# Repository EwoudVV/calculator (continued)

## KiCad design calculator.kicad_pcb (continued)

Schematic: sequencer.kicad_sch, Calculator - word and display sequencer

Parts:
C301, C302, C303, C304, C305, C306, C307, C308, C309, C310, C311, C312, C313, C314, C315, C316, C317, C318, C319, C320: 100n; C_0603_1608Metric
U301, U302: SN74HC163DR; SOIC-16_3.9x9.9mm_P1.27mm
U303: CD74HC173M96; SOIC-16_3.9x9.9mm_P1.27mm
U304: CD74HC157M96; SOIC-16_3.9x9.9mm_P1.27mm
U305: CD74HC139M96; SOIC-16_3.9x9.9mm_P1.27mm
U306, U309, U317: SN74HC04PWR; TSSOP-14_4.4x5mm_P0.65mm
U307, U311, U312, U313, U315, U316, U319: SN74HC08PWR; TSSOP-14_4.4x5mm_P0.65mm
U308, U314, U318: SN74HC32PWR; TSSOP-14_4.4x5mm_P0.65mm
U310: CD74HC27M96; SOIC-14_3.9x8.7mm_P1.27mm
U320: SN74HC74DR; SOIC-14_3.9x8.7mm_P1.27mm

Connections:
+5V: C301.1, C302.1, C303.1, C304.1, C305.1, C306.1, C307.1, C308.1, C309.1, C310.1, C311.1, C312.1, C313.1, C314.1, C315.1, C316.1, C317.1, C318.1, C319.1, C320.1, U301.9 (~PE), U301.10 (CET), U301.16 (VCC), U302.9 (~PE), U302.10 (CET), U302.16 (VCC), U303.16 (VCC), U304.16 (VCC), U305.16 (VCC), U306.14 (VCC), U307.14 (VCC), U308.14 (VCC), U309.14 (VCC), U310.14 (VCC), U311.5, U311.14 (VCC), U312.14 (VCC), U313.14 (VCC), U314.14 (VCC), U315.14 (VCC), U316.14 (VCC), U317.14 (VCC), U318.14 (VCC), U319.14 (VCC), U320.1 (~R), U320.10 (~S), U320.14 (VCC); also elsewhere on the board
/BANK_RESET_N: U320.6 (~Q); also elsewhere on the board
/Sequencer/ACTION_ALLOWED: U307.3, U307.5, U307.10, U315.10, U316.5, U319.2
/Sequencer/CANCEL_N: U306.12, U307.2
/Sequencer/DIGIT_ENABLE: U302.7 (CEP), U313.3
/Sequencer/DIGIT_LAST: U309.3, U311.3, U312.13, U313.5
/Sequencer/DIGIT_LOW_ONES: U307.11, U311.1
/Sequencer/DIGIT_NOT_LAST: U309.4, U313.2
/Sequencer/DIGIT_STEP: U308.11, U313.1
/Sequencer/DISPLAY_ACTIVE: U307.8, U312.1, U312.4, U314.4
/Sequencer/DISPLAY_DONE: U308.10, U312.11
/Sequencer/DISPLAY_ROTATE_A: U314.10, U315.6
/Sequencer/DISPLAY_ROTATE_B: U314.13, U316.3
/Sequencer/DISPLAY_ROTATE_N: U309.6, U313.13
/Sequencer/DISPLAY_ROTATE_W: U316.11, U318.2
/Sequencer/P0_N: U305.4 (O0), U306.1
/Sequencer/P1_N: U305.5 (O1), U306.3
/Sequencer/P2_N: U305.6 (O2), U306.5
/Sequencer/P3_N: U305.7 (O3), U306.9
/Sequencer/PHASE_0: U301.14 (Q0), U305.2 (A0)
/Sequencer/PHASE_1: U301.13 (Q1), U305.3 (A1)
/Sequencer/PHASE_ENABLE: U301.7 (CEP), U314.6
/Sequencer/PHASE_RESET_N: U301.1 (~MR), U313.11
/Sequencer/PH_CLOSE: U306.6, U312.10
/Sequencer/PH_PREP: U306.2, U311.10, U312.2, U314.1
/Sequencer/PH_ROTATE: U306.8, U312.5
/Sequencer/PH_RUN: U306.4, U311.13, U313.4
/Sequencer/POWER_RESET: U303.15 (Mr), U306.10, U308.5
/Sequencer/SEQUENCER_RESET_N: U302.1 (~MR), U309.2, U313.12
/Sequencer/SEQ_ABORT_OR_ADVANCE: U308.3, U308.4
/Sequencer/SEQ_RESET: U308.6, U309.1
/Sequencer/SOURCE_A: U309.10, U315.5
/Sequencer/SOURCE_A_N: U305.12 (O0), U309.11
/Sequencer/SOURCE_B: U309.12, U316.2
/Sequencer/SOURCE_B_N: U305.11 (O1), U309.13
/Sequencer/SOURCE_LOAD: U309.9, U315.3
/Sequencer/SOURCE_LOAD_N: U303.9 (E1), U309.8
/Sequencer/SOURCE_W: U316.13, U317.2
/Sequencer/SOURCE_W_N: U305.10 (O2), U317.1
/Sequencer/WORD_ACTIVE: U307.6, U311.9, U311.12, U312.9, U313.9
/Sequencer/WORD_DONE: U308.9, U312.8
/Sequencer/WORD_LAST_RUN: U313.6, U314.2
/Sequencer/WORD_PHASE_ENABLE: U313.8, U314.5
/Sequencer/WORD_PHASE_STEP: U313.10, U314.3
ALU_STEP: U308.12, U311.11, U314.9, U314.12, U318.1; also elsewhere on the board
A_ROTATE_RIGHT: U314.8; also elsewhere on the board
A_SHIFT_LEFT: U315.8; also elsewhere on the board
A_WRITE_ALU: U315.11; also elsewhere on the board
BANK_CLK: U301.2 (CP), U302.2 (CP), U303.7 (Cp), U320.3 (C); also elsewhere on the board
B_ROTATE_RIGHT: U314.11; also elsewhere on the board
B_SHIFT_LEFT: U316.6; also elsewhere on the board
B_WRITE_ALU: U316.8; also elsewhere on the board
CANCEL: U306.13, U308.2; also elsewhere on the board
DIGIT_FIRST: U310.12, U315.2; also elsewhere on the board
DIGIT_INDEX_0: U302.14 (Q0), U307.12, U310.1; also elsewhere on the board
DIGIT_INDEX_1: U302.13 (Q1), U307.13, U310.2; also elsewhere on the board
DIGIT_INDEX_2: U302.12 (Q2), U310.13, U311.2, U311.4; also elsewhere on the board
DIGIT_UPPER: U311.6; also elsewhere on the board
DISPLAY_MODE: U307.9; also elsewhere on the board
DISPLAY_PREP: U312.3, U315.1; also elsewhere on the board
DISPLAY_ROTATE: U308.13, U309.5, U312.6, U312.12, U315.4, U316.1, U316.12
DISPLAY_SOURCE_0: U303.14 (D0); also elsewhere on the board
DISPLAY_SOURCE_1: U303.13 (D1); also elsewhere on the board
GND: C301.2, C302.2, C303.2, C304.2, C305.2, C306.2, C307.2, C308.2, C309.2, C310.2, C311.2, C312.2, C313.2, C314.2, C315.2, C316.2, C317.2, C318.2, C319.2, C320.2, U301.3 (D0), U301.4 (D1), U301.5 (D2), U301.6 (D3), U301.8 (GND), U302.3 (D0), U302.4 (D1), U302.5 (D2), U302.6 (D3), U302.8 (GND), U303.1 (Oe1), U303.2 (Oe2), U303.8 (GND), U303.10 (E2), U303.11 (D3), U303.12 (D2), U304.8 (GND), U304.15 (E), U305.1 (E), U305.8 (GND), U305.15 (E), U306.7 (GND), U307.7 (GND), U308.7 (GND), U309.7 (GND), U310.3, U310.4, U310.5, U310.7 (GND), U310.9, U310.10, U310.11, U311.7 (GND), U312.7 (GND), U313.7 (GND), U314.7 (GND), U315.7 (GND), U316.7 (GND), U317.3, U317.5, U317.7 (GND), U317.9, U317.11, U317.13, U318.4, U318.5, U318.7 (GND), U318.9, U318.10, U318.12, U318.13, U319.7 (GND), U319.9, U319.10, U319.12, U319.13, U320.7 (GND), U320.11 (C), U320.12 (D), U320.13 (~R); also elsewhere on the board
MAC_BANK_RESET: U320.2 (D); also elsewhere on the board
MAC_SHIFT_A: U315.9; also elsewhere on the board
MAC_SHIFT_B: U316.4; also elsewhere on the board
MAC_SHIFT_W: U319.1; also elsewhere on the board
MAC_WRITE_A: U315.12; also elsewhere on the board
MAC_WRITE_B: U316.9; also elsewhere on the board
MAC_WRITE_W: U319.4; also elsewhere on the board
MAC_X_0: U304.3 (I1a); also elsewhere on the board
MAC_X_1: U304.6 (I1b); also elsewhere on the board
MAC_Y_0: U304.10 (I1c), U304.11 (I0c); also elsewhere on the board
MAC_Y_1: U304.13 (I1d), U304.14 (I0d); also elsewhere on the board
POWER_RESET_N: U306.11, U307.1, U320.4 (~S); also elsewhere on the board
SAVED_SOURCE_0: U303.3 (Q0), U304.2 (I0a), U305.14 (A0)
SAVED_SOURCE_1: U303.4 (Q1), U304.5 (I0b), U305.13 (A1)
SEQUENCE_DONE: U308.8; also elsewhere on the board
STATE_ADVANCE: U308.1; also elsewhere on the board
WORD_MODE: U304.1 (S), U307.4, U315.13, U316.10, U319.5; also elsewhere on the board
WORD_PREP: U311.8; also elsewhere on the board
W_ROTATE_RIGHT: U318.3; also elsewhere on the board
W_SHIFT_LEFT: U319.3; also elsewhere on the board
W_WRITE_ALU: U319.6; also elsewhere on the board
X_SELECT_0: U304.4 (Za); also elsewhere on the board
X_SELECT_1: U304.7 (Zb); also elsewhere on the board
Y_SELECT_0: U304.9 (Zc); also elsewhere on the board
Y_SELECT_1: U304.12 (Zd); also elsewhere on the board

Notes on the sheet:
Phase counter
Eight internal digits
Hold display source through Clear
Adder / display bus selection
Close the display latch before clearing banks
Gate power and local decoupling

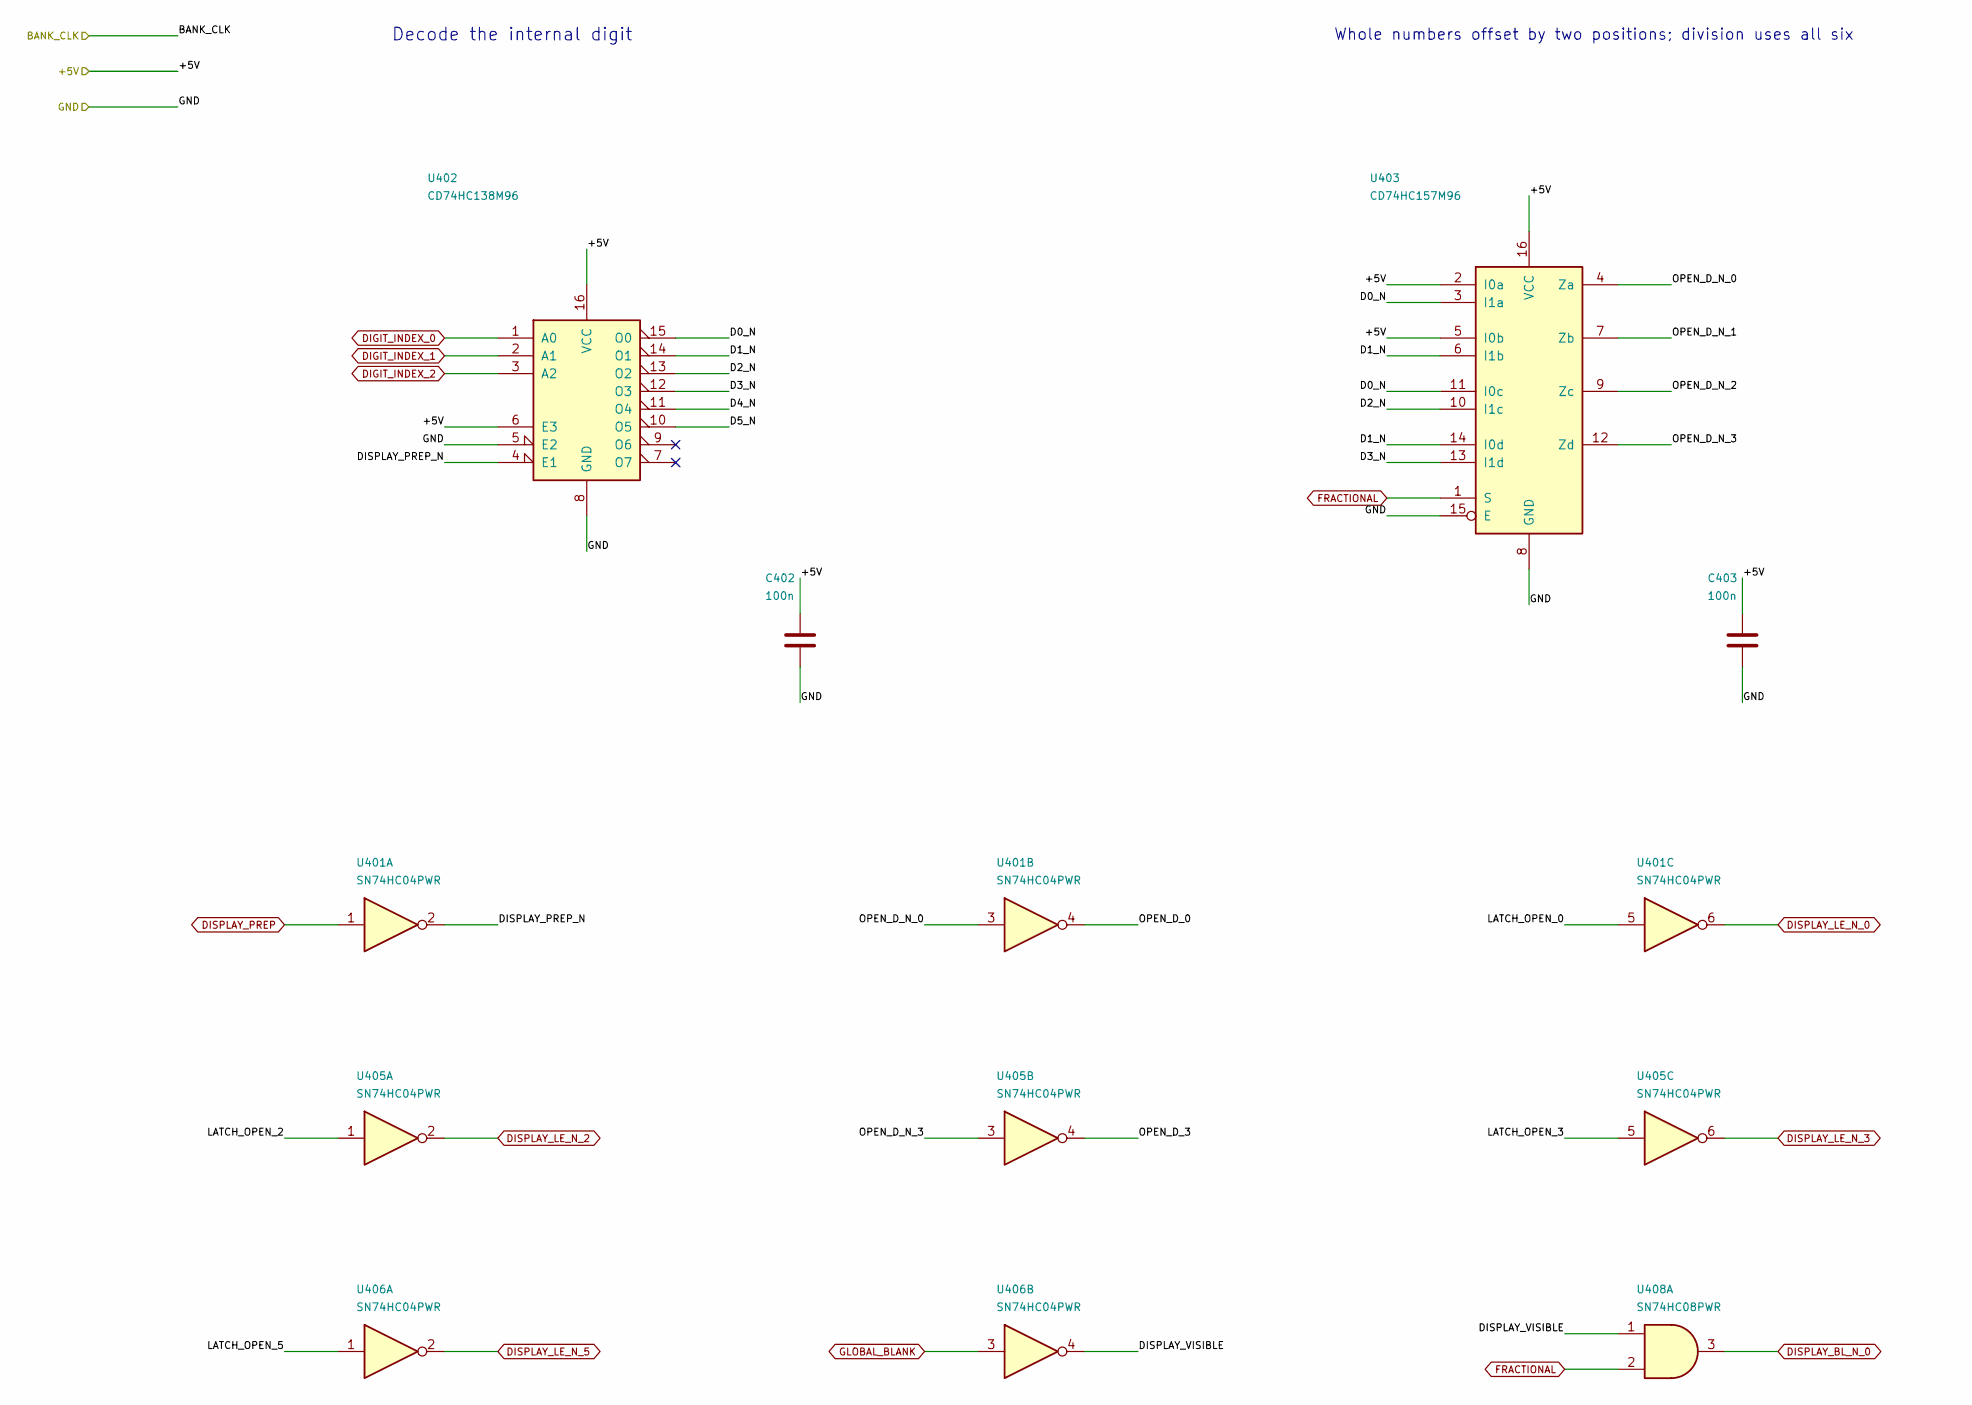
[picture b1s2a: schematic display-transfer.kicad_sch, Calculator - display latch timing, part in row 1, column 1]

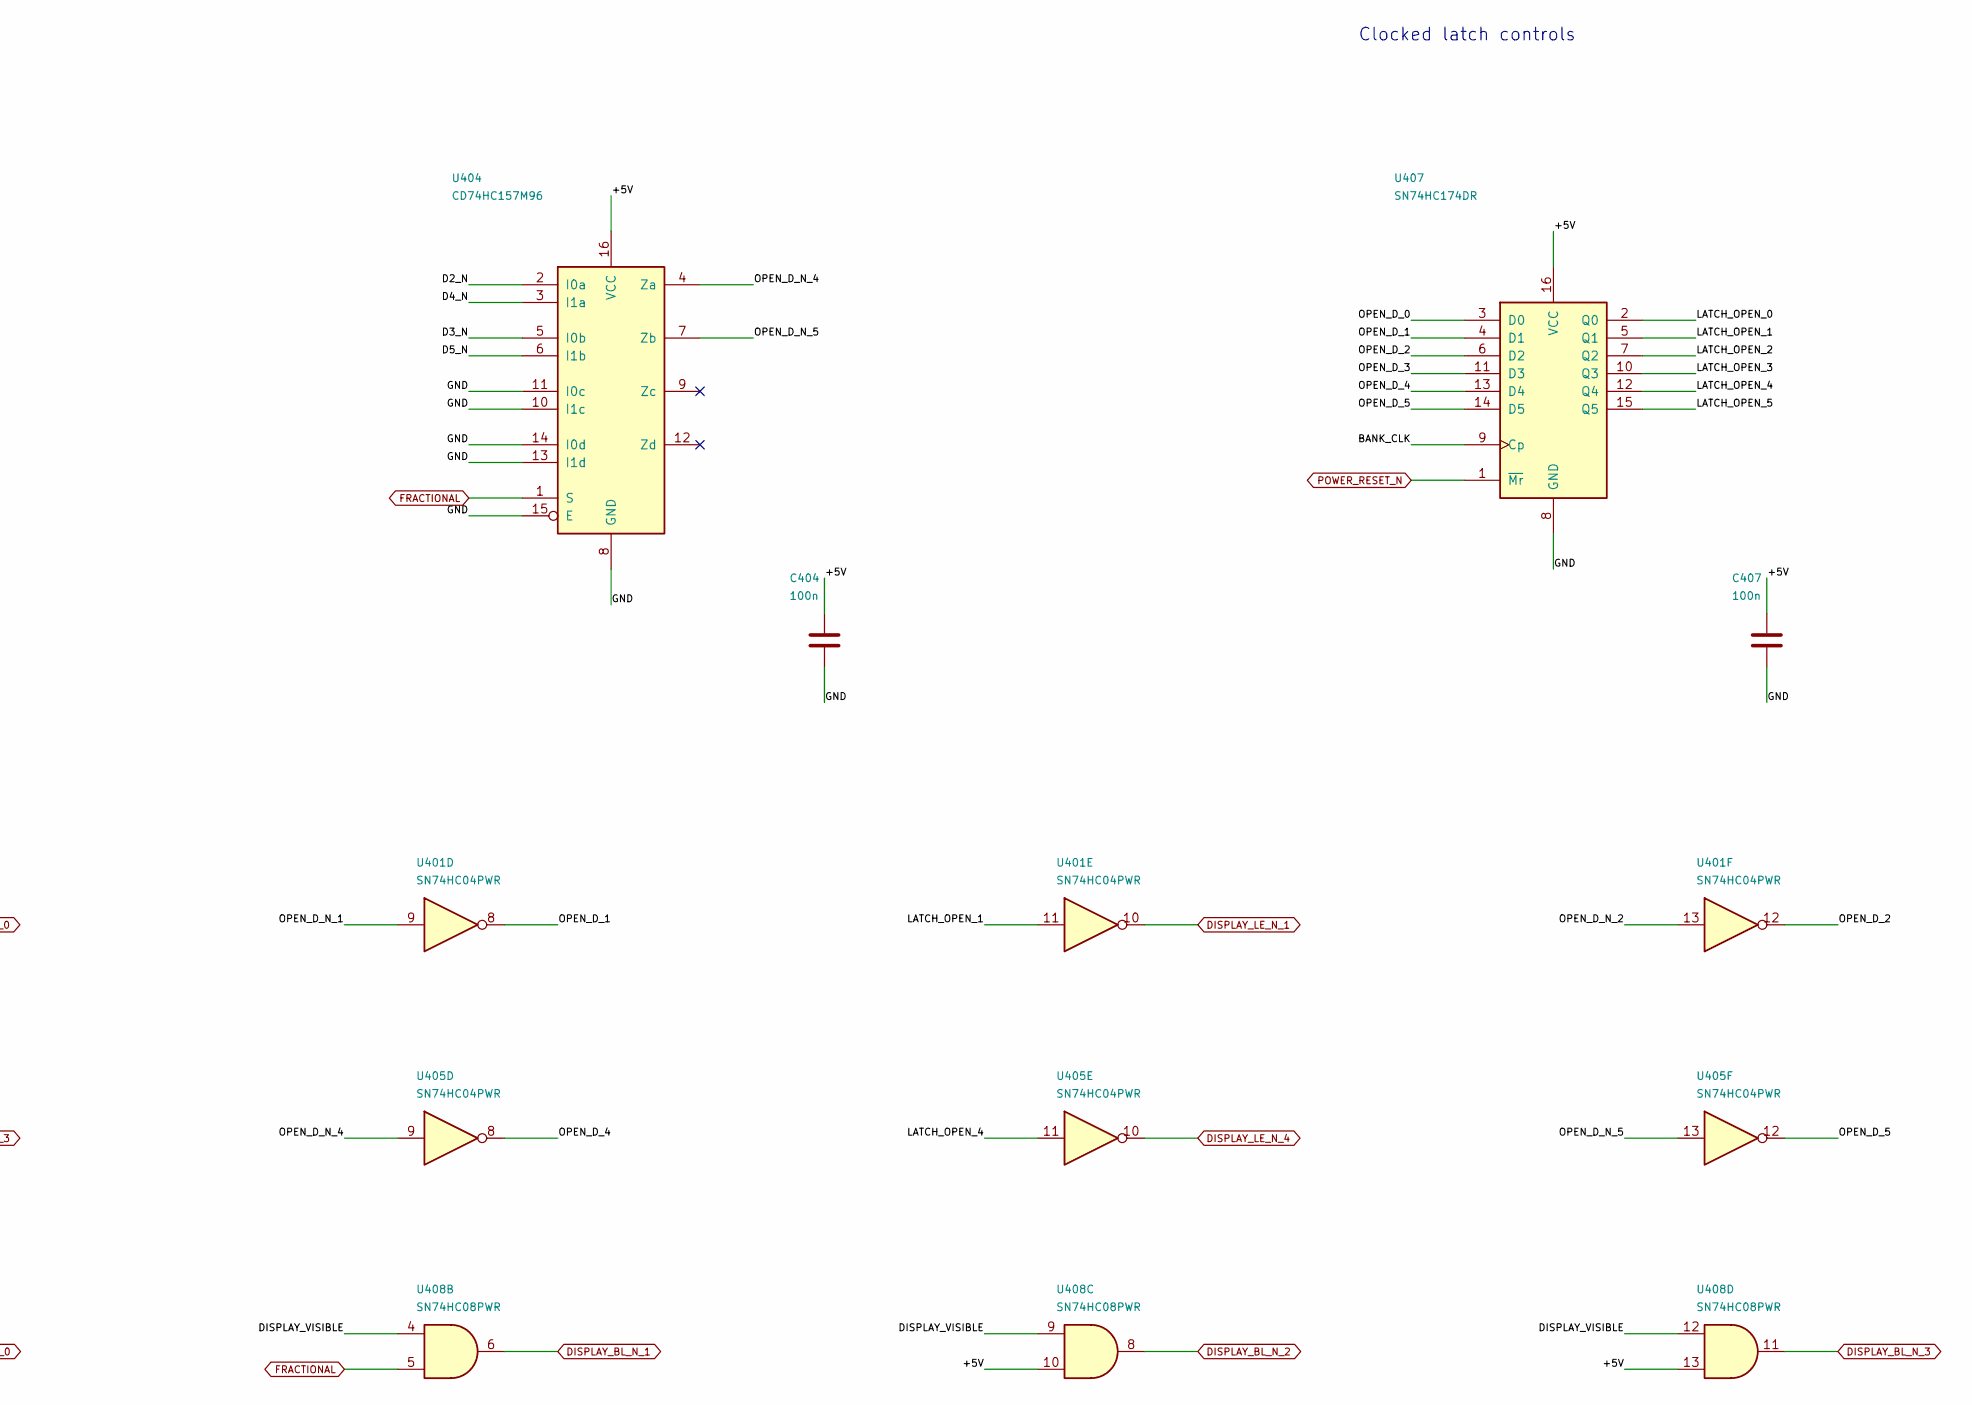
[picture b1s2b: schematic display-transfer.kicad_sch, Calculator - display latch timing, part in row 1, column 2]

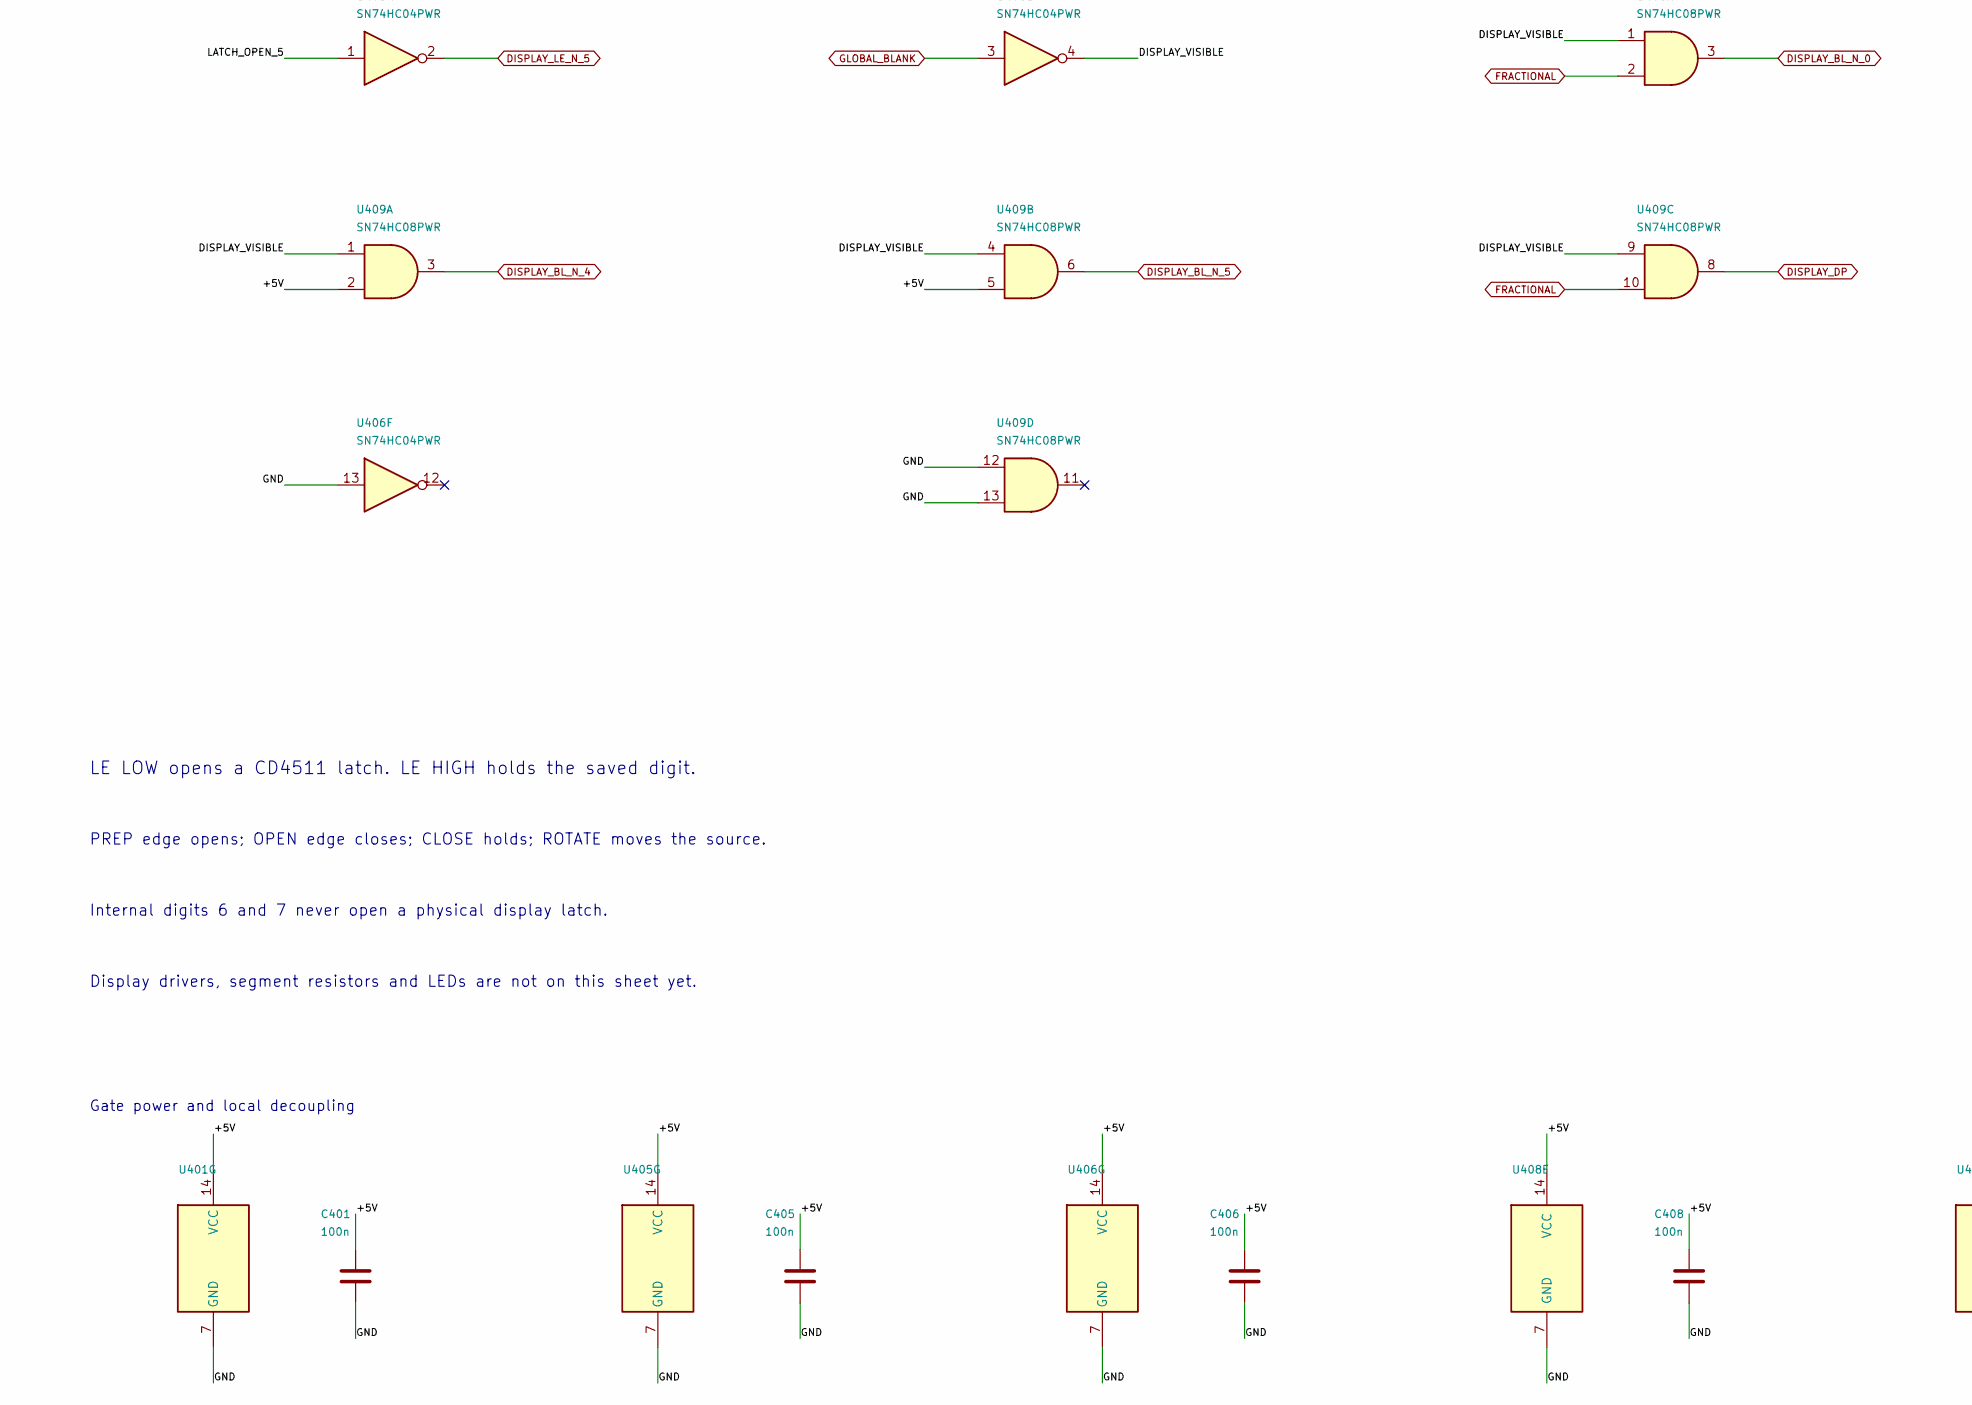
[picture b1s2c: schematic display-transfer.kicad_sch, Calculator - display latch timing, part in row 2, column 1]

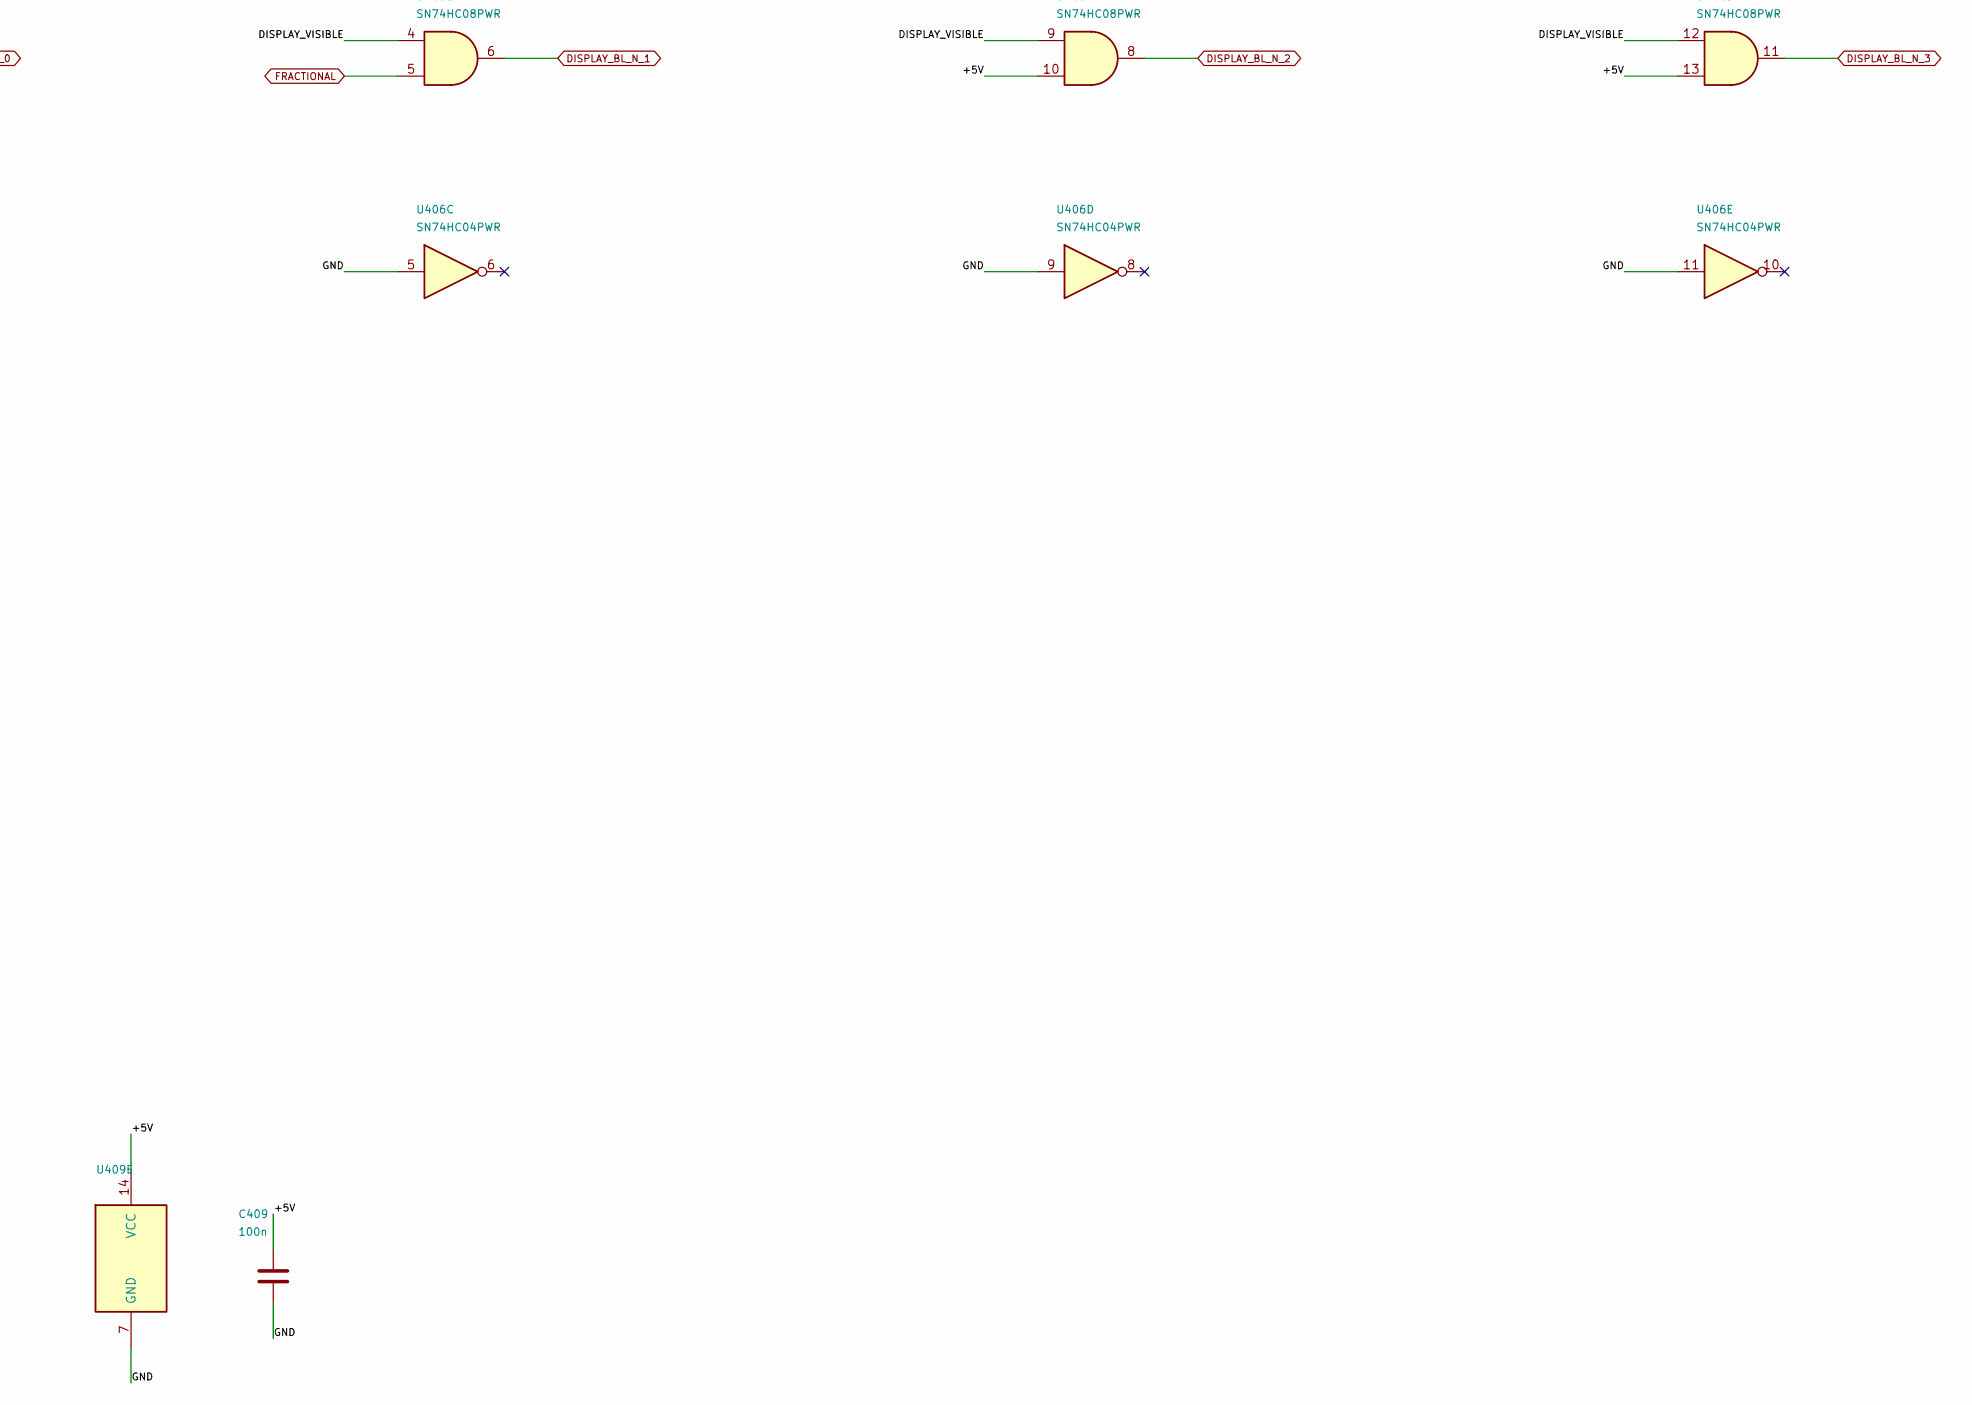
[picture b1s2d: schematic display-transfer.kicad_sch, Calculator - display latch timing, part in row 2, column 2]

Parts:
C401, C402, C403, C404, C405, C406, C407, C408, C409: 100n; C_0603_1608Metric
U401, U405, U406: SN74HC04PWR; TSSOP-14_4.4x5mm_P0.65mm
U402: CD74HC138M96; SOIC-16_3.9x9.9mm_P1.27mm
U403, U404: CD74HC157M96; SOIC-16_3.9x9.9mm_P1.27mm
U407: SN74HC174DR; SOIC-16_3.9x9.9mm_P1.27mm
U408, U409: SN74HC08PWR; TSSOP-14_4.4x5mm_P0.65mm

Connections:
+5V: C401.1, C402.1, C403.1, C404.1, C405.1, C406.1, C407.1, C408.1, C409.1, U401.14 (VCC), U402.6 (E3), U402.16 (VCC), U403.2 (I0a), U403.5 (I0b), U403.16 (VCC), U404.16 (VCC), U405.14 (VCC), U406.14 (VCC), U407.16 (VCC), U408.10, U408.13, U408.14 (VCC), U409.2, U409.5, U409.14 (VCC); also elsewhere on the board
/Display timing/D0_N: U402.15 (O0), U403.3 (I1a), U403.11 (I0c)
/Display timing/D1_N: U402.14 (O1), U403.6 (I1b), U403.14 (I0d)
/Display timing/D2_N: U402.13 (O2), U403.10 (I1c), U404.2 (I0a)
/Display timing/D3_N: U402.12 (O3), U403.13 (I1d), U404.5 (I0b)
/Display timing/D4_N: U402.11 (O4), U404.3 (I1a)
/Display timing/D5_N: U402.10 (O5), U404.6 (I1b)
/Display timing/DISPLAY_PREP_N: U401.2, U402.4 (E1)
/Display timing/DISPLAY_VISIBLE: U406.4, U408.1, U408.4, U408.9, U408.12, U409.1, U409.4, U409.9
/Display timing/LATCH_OPEN_0: U401.5, U407.2 (Q0)
/Display timing/LATCH_OPEN_1: U401.11, U407.5 (Q1)
/Display timing/LATCH_OPEN_2: U405.1, U407.7 (Q2)
/Display timing/LATCH_OPEN_3: U405.5, U407.10 (Q3)
/Display timing/LATCH_OPEN_4: U405.11, U407.12 (Q4)
/Display timing/LATCH_OPEN_5: U406.1, U407.15 (Q5)
/Display timing/OPEN_D_0: U401.4, U407.3 (D0)
/Display timing/OPEN_D_1: U401.8, U407.4 (D1)
/Display timing/OPEN_D_2: U401.12, U407.6 (D2)
/Display timing/OPEN_D_3: U405.4, U407.11 (D3)
/Display timing/OPEN_D_4: U405.8, U407.13 (D4)
/Display timing/OPEN_D_5: U405.12, U407.14 (D5)
/Display timing/OPEN_D_N_0: U401.3, U403.4 (Za)
/Display timing/OPEN_D_N_1: U401.9, U403.7 (Zb)
/Display timing/OPEN_D_N_2: U401.13, U403.9 (Zc)
/Display timing/OPEN_D_N_3: U403.12 (Zd), U405.3
/Display timing/OPEN_D_N_4: U404.4 (Za), U405.9
/Display timing/OPEN_D_N_5: U404.7 (Zb), U405.13
BANK_CLK: U407.9 (Cp); also elsewhere on the board
DIGIT_INDEX_0: U402.1 (A0); also elsewhere on the board
DIGIT_INDEX_1: U402.2 (A1); also elsewhere on the board
DIGIT_INDEX_2: U402.3 (A2); also elsewhere on the board
DISPLAY_BL_N_0: U408.3; also elsewhere on the board
DISPLAY_BL_N_1: U408.6; also elsewhere on the board
DISPLAY_BL_N_2: U408.8; also elsewhere on the board
DISPLAY_BL_N_3: U408.11; also elsewhere on the board
DISPLAY_BL_N_4: U409.3; also elsewhere on the board
DISPLAY_BL_N_5: U409.6; also elsewhere on the board
DISPLAY_DP: U409.8; also elsewhere on the board
DISPLAY_LE_N_0: U401.6; also elsewhere on the board
DISPLAY_LE_N_1: U401.10; also elsewhere on the board
DISPLAY_LE_N_2: U405.2; also elsewhere on the board
DISPLAY_LE_N_3: U405.6; also elsewhere on the board
DISPLAY_LE_N_4: U405.10; also elsewhere on the board
DISPLAY_LE_N_5: U406.2; also elsewhere on the board
DISPLAY_PREP: U401.1; also elsewhere on the board
FRACTIONAL: U403.1 (S), U404.1 (S), U408.2, U408.5, U409.10; also elsewhere on the board
GLOBAL_BLANK: U406.3; also elsewhere on the board
GND: C401.2, C402.2, C403.2, C404.2, C405.2, C406.2, C407.2, C408.2, C409.2, U401.7 (GND), U402.5 (E2), U402.8 (GND), U403.8 (GND), U403.15 (E), U404.8 (GND), U404.10 (I1c), U404.11 (I0c), U404.13 (I1d), U404.14 (I0d), U404.15 (E), U405.7 (GND), U406.5, U406.7 (GND), U406.9, U406.11, U406.13, U407.8 (GND), U408.7 (GND), U409.7 (GND), U409.12, U409.13; also elsewhere on the board
POWER_RESET_N: U407.1 (~Mr); also elsewhere on the board

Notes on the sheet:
Decode the internal digit
Whole numbers offset by two positions; division uses all six
Clocked latch controls
LE LOW opens a CD4511 latch. LE HIGH holds the saved digit.
PREP edge opens; OPEN edge closes; CLOSE holds; ROTATE moves the source.
Internal digits 6 and 7 never open a physical display latch.
Display drivers, segment resistors and LEDs are not on this sheet yet.
Gate power and local decoupling

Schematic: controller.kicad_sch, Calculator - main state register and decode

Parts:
C501, C502, C503, C504, C505, C506, C507, C508, C509, C510: 100n; C_0603_1608Metric
U501, U502: SN74HC163DR; SOIC-16_3.9x9.9mm_P1.27mm
U503, U504, U505, U506, U507, U508, U509, U510: CD74HC138M96; SOIC-16_3.9x9.9mm_P1.27mm

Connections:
+5V: C501.1, C502.1, C503.1, C504.1, C505.1, C506.1, C507.1, C508.1, C509.1, C510.1, U501.1 (~MR), U501.10 (CET), U501.16 (VCC), U502.1 (~MR), U502.16 (VCC), U503.16 (VCC), U504.16 (VCC), U505.16 (VCC), U506.16 (VCC), U507.16 (VCC), U508.16 (VCC), U509.16 (VCC), U510.16 (VCC); also elsewhere on the board
/Main controller/STATE_GROUP_0_N: U503.15 (O0), U504.4 (E1)
/Main controller/STATE_GROUP_1_N: U503.14 (O1), U505.4 (E1)
/Main controller/STATE_GROUP_2_N: U503.13 (O2), U506.4 (E1)
/Main controller/STATE_GROUP_3_N: U503.12 (O3), U507.4 (E1)
/Main controller/STATE_GROUP_4_N: U503.11 (O4), U508.4 (E1)
/Main controller/STATE_GROUP_5_N: U503.10 (O5), U509.4 (E1)
/Main controller/STATE_GROUP_6_N: U503.9 (O6), U510.4 (E1)
BANK_CLK: U501.2 (CP), U502.2 (CP); also elsewhere on the board
GND: C501.2, C502.2, C503.2, C504.2, C505.2, C506.2, C507.2, C508.2, C509.2, C510.2, U501.8 (GND), U502.5 (D2), U502.6 (D3), U502.8 (GND), U503.4 (E1), U503.5 (E2), U503.8 (GND), U504.5 (E2), U504.8 (GND), U505.5 (E2), U505.8 (GND), U506.5 (E2), U506.8 (GND), U507.5 (E2), U507.8 (GND), U508.5 (E2), U508.8 (GND), U509.5 (E2), U509.8 (GND), U510.5 (E2), U510.8 (GND); also elsewhere on the board
MAIN_JUMP_0: U501.3 (D0); also elsewhere on the board
MAIN_JUMP_1: U501.4 (D1); also elsewhere on the board
MAIN_JUMP_2: U501.5 (D2); also elsewhere on the board
MAIN_JUMP_3: U501.6 (D3); also elsewhere on the board
MAIN_JUMP_4: U502.3 (D0); also elsewhere on the board
MAIN_JUMP_5: U502.4 (D1); also elsewhere on the board
MAIN_LOAD_N: U501.9 (~PE), U502.9 (~PE); also elsewhere on the board
MAIN_LOW_TC: U501.15 (TC), U502.10 (CET)
POWER_RESET_N: U503.6 (E3), U504.6 (E3), U505.6 (E3), U506.6 (E3), U507.6 (E3), U508.6 (E3), U509.6 (E3), U510.6 (E3); also elsewhere on the board
STATE_0: U501.14 (Q0), U504.1 (A0), U505.1 (A0), U506.1 (A0), U507.1 (A0), U508.1 (A0), U509.1 (A0), U510.1 (A0)
STATE_1: U501.13 (Q1), U504.2 (A1), U505.2 (A1), U506.2 (A1), U507.2 (A1), U508.2 (A1), U509.2 (A1), U510.2 (A1)
STATE_2: U501.12 (Q2), U504.3 (A2), U505.3 (A2), U506.3 (A2), U507.3 (A2), U508.3 (A2), U509.3 (A2), U510.3 (A2)
STATE_3: U501.11 (Q3), U503.1 (A0)
STATE_4: U502.14 (Q0), U503.2 (A1)
STATE_5: U502.13 (Q1), U503.3 (A2)
STATE_6: U502.12 (Q2); also elsewhere on the board
STATE_7: U502.11 (Q3); also elsewhere on the board
STATE_ADVANCE: U501.7 (CEP), U502.7 (CEP); also elsewhere on the board
STATE_GROUP_7_N: U503.7 (O7); also elsewhere on the board
S_ADD_CHECK_N: U504.13 (O2); also elsewhere on the board
S_ADD_N: U504.14 (O1); also elsewhere on the board
S_CLEAR_DISPLAY_N: U509.13 (O2); also elsewhere on the board
S_DIV_ZERO_N: U509.11 (O4); also elsewhere on the board
S_DONE_A_N: U509.14 (O1); also elsewhere on the board
S_DONE_W_N: U509.15 (O0); also elsewhere on the board
S_D_APPEND_N: U507.10 (O5); also elsewhere on the board
S_D_BORROW_N: U507.7 (O7); also elsewhere on the board
S_D_B_ZERO_N: U506.7 (O7); also elsewhere on the board
S_D_CLEAR_N: U507.13 (O2); also elsewhere on the board
S_D_DOUBLE_N: U508.11 (O4); also elsewhere on the board
S_D_INCREMENT_N: U508.7 (O7); also elsewhere on the board
S_D_Q_INC_N: U508.15 (O0); also elsewhere on the board
S_D_Q_RESET_N: U507.11 (O4); also elsewhere on the board
S_D_RESTORE_N: U508.14 (O1); also elsewhere on the board
S_D_ROUND_COMPARE_N: U508.10 (O5); also elsewhere on the board
S_D_ROUND_N: U508.9 (O6); also elsewhere on the board
S_D_SCALE_1_N: U507.15 (O0); also elsewhere on the board
S_D_SCALE_2_N: U507.14 (O1); also elsewhere on the board
S_D_STAGE_N: U508.12 (O3); also elsewhere on the board
S_D_START_N: U507.12 (O3); also elsewhere on the board
S_D_STORE_Q_N: U508.13 (O2); also elsewhere on the board
S_D_SUB_N: U507.9 (O6); also elsewhere on the board
S_D_TEST_B_N: U506.9 (O6); also elsewhere on the board
S_E_CLEAR_ASSERT_N: U510.14 (O1); also elsewhere on the board
S_E_CLEAR_WAIT_N: U510.13 (O2); also elsewhere on the board
S_E_DISPLAY_A_N: U509.7 (O7); also elsewhere on the board
S_E_DISPLAY_B_N: U510.15 (O0); also elsewhere on the board
S_E_NEW_CLEAR_N: U510.12 (O3); also elsewhere on the board
S_E_NEW_WAIT_N: U510.11 (O4); also elsewhere on the board
S_E_SHIFT_A_N: U509.10 (O5); also elsewhere on the board
S_E_SHIFT_B_N: U509.9 (O6); also elsewhere on the board
S_IDLE_N: U504.15 (O0); also elsewhere on the board
S_INVALID_53_N: U510.10 (O5); also elsewhere on the board
S_INVALID_54_N: U510.9 (O6); also elsewhere on the board
S_INVALID_55_N: U510.7 (O7); also elsewhere on the board
S_M_ADD_N: U506.14 (O1); also elsewhere on the board
S_M_AGAIN_N: U506.11 (O4); also elsewhere on the board
S_M_A_ZERO_N: U505.15 (O0); also elsewhere on the board
S_M_B_ZERO_N: U505.13 (O2); also elsewhere on the board
S_M_CLEAR_N: U506.15 (O0); also elsewhere on the board
S_M_COMPARE_N: U505.12 (O3); also elsewhere on the board
S_M_DEC_N: U506.12 (O3); also elsewhere on the board
S_M_LIMIT_N: U506.13 (O2); also elsewhere on the board
S_M_ORDER_N: U505.11 (O4); also elsewhere on the board
S_M_SAVE_N: U505.10 (O5); also elsewhere on the board
S_M_SWAP_A_N: U505.9 (O6); also elsewhere on the board
S_M_SWAP_B_N: U505.7 (O7); also elsewhere on the board
S_M_TEST_A_N: U504.7 (O7); also elsewhere on the board
S_M_TEST_B_N: U505.14 (O1); also elsewhere on the board
S_NEGATE_N: U504.10 (O5); also elsewhere on the board
S_OVERFLOW_N: U509.12 (O3); also elsewhere on the board
S_SET_MINUS_N: U504.9 (O6); also elsewhere on the board
S_SUB_CHECK_N: U504.11 (O4); also elsewhere on the board
S_SUB_N: U504.12 (O3); also elsewhere on the board
S_ZERO_W_N: U506.10 (O5); also elsewhere on the board

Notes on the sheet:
States 0 to 7
States 8 to 15
States 16 to 23
States 24 to 31
States 32 to 39
States 40 to 47
States 48 to 55
Count forward, or load a fixed branch target
Group decode
Clock and power reset are external. No control ROM.
